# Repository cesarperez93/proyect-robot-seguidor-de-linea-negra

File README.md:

# proyect-robot-seguidor-de-linea-negra

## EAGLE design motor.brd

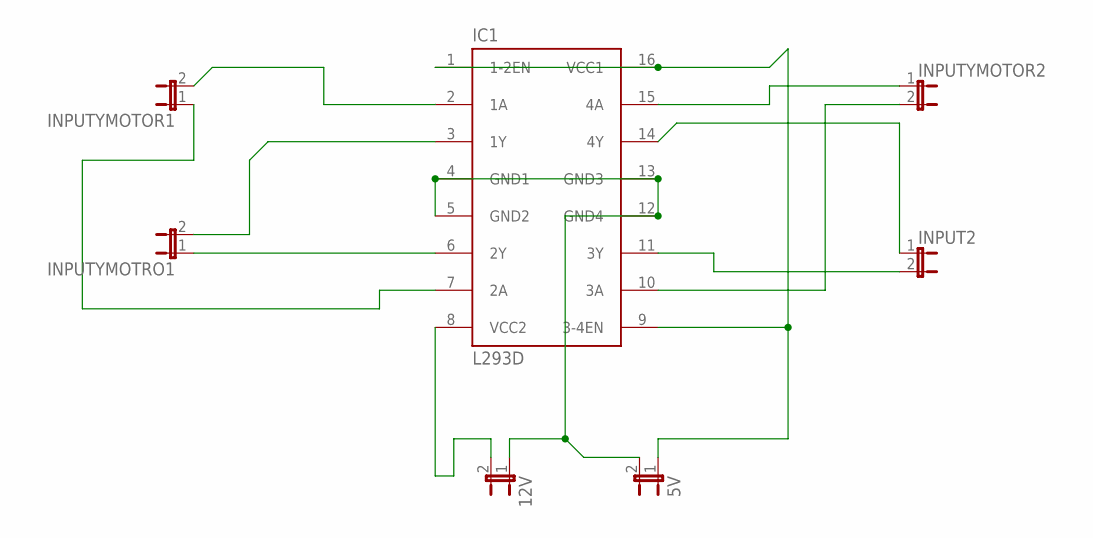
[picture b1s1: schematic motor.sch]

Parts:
5V, 12V: JP1E; JP1
IC1: L293D; DIL16
INPUT2: JP1E; JP1
INPUTYMOTOR1, INPUTYMOTOR2: JP1E; JP1
INPUTYMOTRO1: JP1E; JP1

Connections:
unnamed: IC1.2 (1A), INPUTYMOTOR1.2
unnamed: IC1.7 (2A), INPUTYMOTOR1.1
unnamed: IC1.3 (1Y), INPUTYMOTRO1.2
unnamed: IC1.6 (2Y), INPUTYMOTRO1.1
unnamed: 5V.2, 12V.1, IC1.4 (GND1), IC1.5 (GND2), IC1.12 (GND4), IC1.13 (GND3)
unnamed: 12V.2, IC1.8 (VCC2)
unnamed: 5V.1, IC1.1 (1-2EN), IC1.9 (3-4EN), IC1.16 (VCC1)
unnamed: IC1.15 (4A), INPUTYMOTOR2.1
unnamed: IC1.10 (3A), INPUTYMOTOR2.2
unnamed: IC1.11 (3Y), INPUT2.2
unnamed: IC1.14 (4Y), INPUT2.1

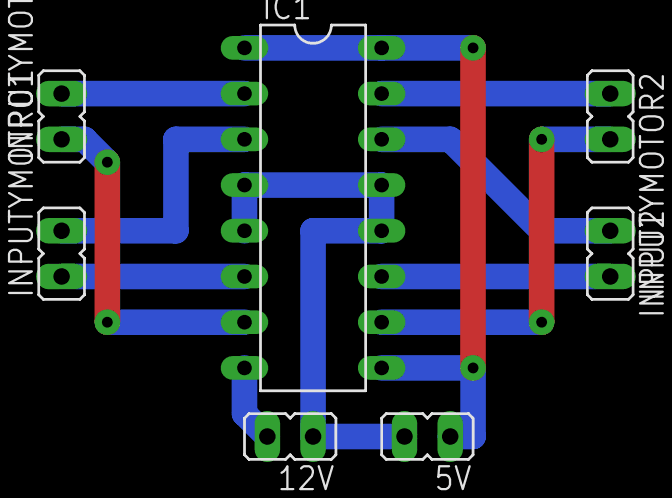
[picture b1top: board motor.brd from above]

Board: 2 copper layers, 7 parts (0 on the bottom side), 11 nets.

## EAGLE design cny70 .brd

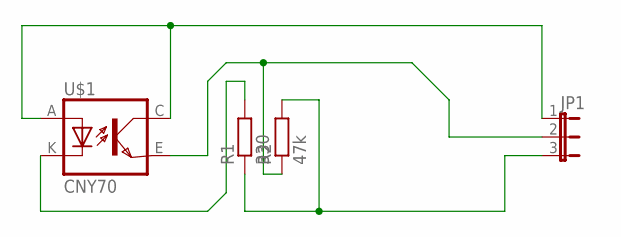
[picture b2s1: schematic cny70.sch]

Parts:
JP1: JP2E; JP2
R1: 330; 0207/10
R2: 47k; 0207/10
U$1: CNY70; 4

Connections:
unnamed: JP1.1, U$1.A, U$1.C (COL)
unnamed: R1.2, U$1.K (C)
unnamed: JP1.3, R1.1, R2.2
unnamed: JP1.2, R2.1, U$1.E (EMI)

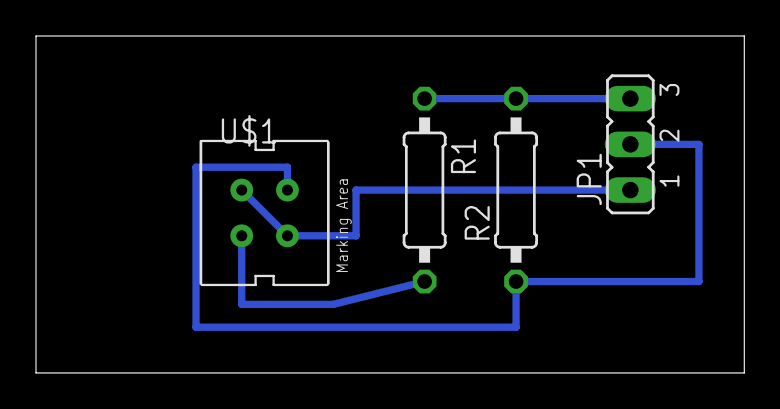
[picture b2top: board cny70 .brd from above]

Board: 2 copper layers, 39.4 x 18.7 mm, 4 parts (0 on the bottom side), 4 nets.

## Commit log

2018-06-07 proyecto carro
    archivos
2018-06-10 diagramas cny70
2018-06-10 esquematico
2018-06-12 chasis
2018-06-13 documento
